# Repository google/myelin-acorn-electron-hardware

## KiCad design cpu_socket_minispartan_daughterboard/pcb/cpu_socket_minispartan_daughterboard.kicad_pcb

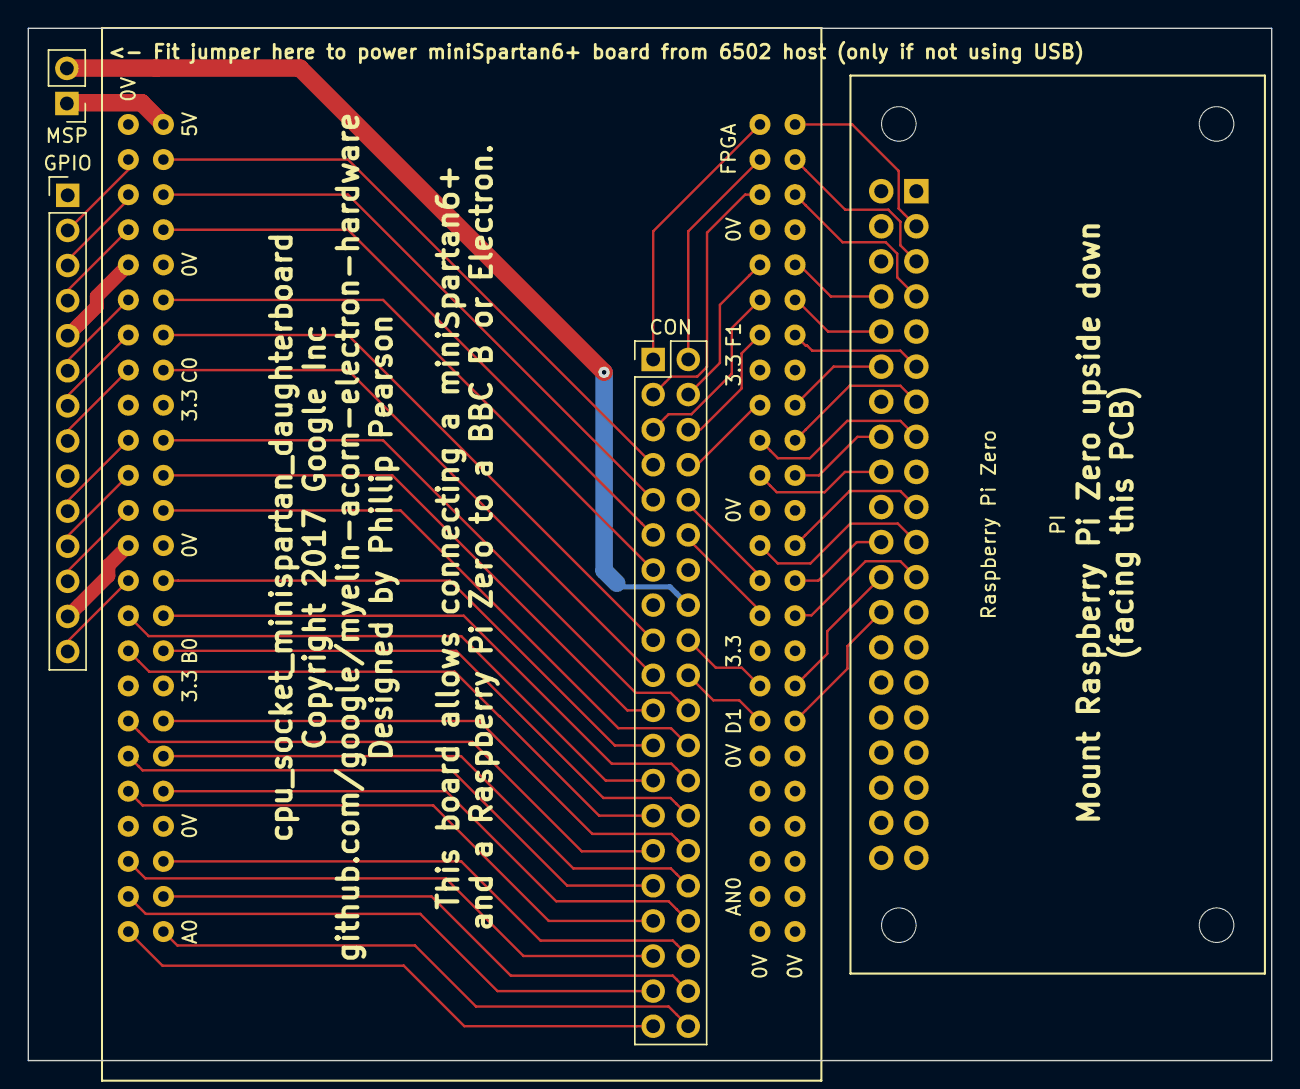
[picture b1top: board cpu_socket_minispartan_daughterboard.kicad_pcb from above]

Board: 2 copper layers, 90.0 x 74.7 mm, 5 parts (0 on the bottom side), 69 nets.

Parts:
CON: 2x20 connector for daughterboard; Pin_Header_Straight_2x20_Pitch2.54mm
FPGA: miniSpartan6+ board; scarab_mini_spartan_6_lx25
GPIO: some GPIO pins; Pin_Header_Straight_1x14_Pitch2.54mm
MSP: bbc to minispartan 5v; Pin_Header_Straight_1x02_Pitch2.54mm
PI: Raspberry Pi Zero; raspberry_pi_zero_flipped

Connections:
GND: CON.14, FPGA.GNDa, FPGA.GNDb, FPGA.GNDc, FPGA.GNDd, FPGA.GNDe, FPGA.GNDf, FPGA.GNDg, FPGA.GNDh, FPGA.GNDi, FPGA.GNDj, FPGA.GNDk, FPGA.GNDl, FPGA.GNDm, FPGA.GNDn, GPIO.1, GPIO.9, PI.9, PI.14, PI.20, PI.25
ext_5V: CON.16, MSP.2
ext_A0: CON.25, FPGA.B3
ext_A1: CON.26, FPGA.B2
ext_A2: CON.27, FPGA.B1
ext_A3: CON.28, FPGA.B0
ext_A4: CON.29, FPGA.A11
ext_A5: CON.30, FPGA.A10
ext_A6: CON.31, FPGA.A9
ext_A7: CON.32, FPGA.A8
ext_A8: CON.33, FPGA.A7
ext_A9: CON.34, FPGA.A6
ext_A10: CON.35, FPGA.A5
ext_A11: CON.36, FPGA.A4
ext_A12: CON.37, FPGA.A3
ext_A13: CON.38, FPGA.A2
ext_A14: CON.39, FPGA.A1
ext_A15: CON.40, FPGA.A0
ext_D0: CON.17, FPGA.C2
ext_D1: CON.18, FPGA.D3
ext_D2: CON.19, FPGA.C0
ext_D3: CON.20, FPGA.D1
ext_D4: CON.21, FPGA.B8
ext_D5: CON.22, FPGA.B10
ext_D6: CON.23, FPGA.B4
ext_D7: CON.24, FPGA.B6
ext_GP0: CON.1, FPGA.F11
ext_GP1: CON.2, FPGA.F9
ext_GP2: CON.3, FPGA.F7
ext_GP3: CON.4, FPGA.F5
ext_GP4: CON.5, FPGA.F3
ext_GP5: CON.6, FPGA.F1
ext_GP6: CON.7, FPGA.C10
ext_GP7: CON.8, FPGA.E11
ext_GP8: CON.9, FPGA.C8
ext_GP9: CON.10, FPGA.E3
ext_GP10: CON.11, FPGA.C6
ext_GP11: CON.12, FPGA.E1
ext_GP12: CON.13, FPGA.C4
minispartan_3V3c: FPGA.3V3c, GPIO.13
minispartan_3V3e: FPGA.3V3e, GPIO.5
minispartan_5v: FPGA.5V0, MSP.1
minispartan_B5: FPGA.B5, GPIO.14
minispartan_B7: FPGA.B7, GPIO.12
minispartan_B9: FPGA.B9, GPIO.11
minispartan_B11: FPGA.B11, GPIO.10
minispartan_C1: FPGA.C1, GPIO.8
minispartan_C3: FPGA.C3, GPIO.7
minispartan_C5: FPGA.C5, GPIO.6
minispartan_C7: FPGA.C7, GPIO.4
minispartan_C9: FPGA.C9, GPIO.3
minispartan_C11: FPGA.C11, GPIO.2
pi_serial_RX: FPGA.F2, PI.10
pi_serial_TX: FPGA.F4, PI.8
tube_A0: FPGA.E8, PI.13
tube_A1: FPGA.F10, PI.3
tube_A2: FPGA.F8, PI.5
tube_D0: FPGA.D2, PI.24
tube_D1: FPGA.E5, PI.21
tube_D2: FPGA.E4, PI.19
tube_D3: FPGA.E0, PI.23
tube_D4: FPGA.E9, PI.15
tube_D5: FPGA.E6, PI.16
tube_D6: FPGA.E7, PI.18
tube_D7: FPGA.E2, PI.22
tube_PHI0: FPGA.D0, PI.26
tube_RnW: FPGA.E10, PI.12
tube_nRST: FPGA.F6, PI.7
tube_nTUBE: FPGA.F0, PI.11

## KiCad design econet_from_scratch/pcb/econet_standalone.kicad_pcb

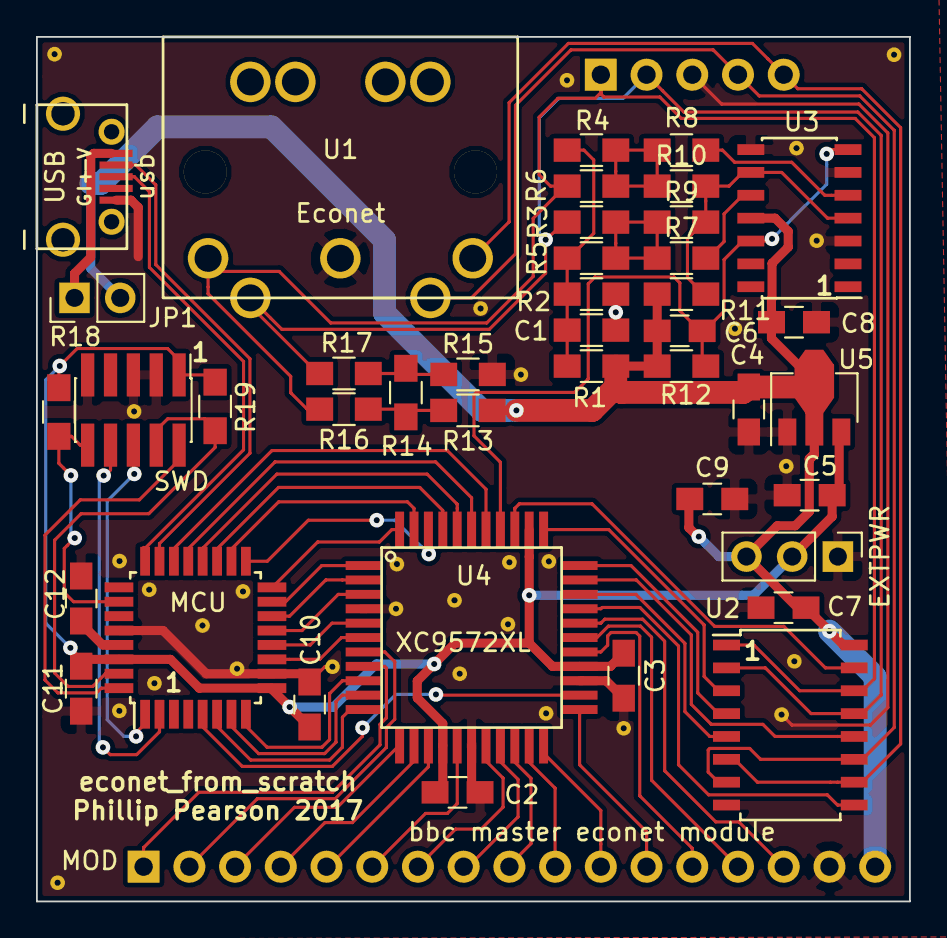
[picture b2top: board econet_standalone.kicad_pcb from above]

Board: 2 copper layers, 48.5 x 48.0 mm, 72 parts (0 on the bottom side), 62 nets.

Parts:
C1: 10u; R_0805_HandSoldering
C2, C3, C7, C8, C10, C11: 100n; C_0805_HandSoldering
C4, C5, C12: 1u; C_0805_HandSoldering
C6: 10n; C_0805_HandSoldering
C9: 10u; C_0805_HandSoldering
EXTPWR: ext pwr; Pin_Header_Straight_1x03_Pitch2.54mm
JP1: USB power; Pin_Header_Straight_1x02_Pitch2.54mm
MCU: ATSAMD21E18A; TQFP-32_7x7mm_Pitch0.8mm
MOD: bbc master econet module; bbc_master_econet_module
R1: 1k5; R_0805_HandSoldering
R2, R12, R13, R15, R19: 1k; R_0805_HandSoldering
R3, R4: 100k; R_0805_HandSoldering
R5, R6, R18: 10k; R_0805_HandSoldering
R7, R8, R9, R10: 56k; R_0805_HandSoldering
R11: 1M5; R_0805_HandSoldering
R14: 220R; R_0805_HandSoldering
R16, R17: 56R; R_0805_HandSoldering
SWD: swd; Pin_Header_Straight_2x05_Pitch1.27mm_SMD
U1: Econet; din_5_econet_pcb_mount
U2: SN65C1168; SOIC-16W_5.3x10.2mm_Pitch1.27mm
U3: LM319; SOIC-14_3.9x8.7mm_Pitch1.27mm
U4: XC9572XL; xilinx_vqg44
U5: MCP1700T-3302E/MB; SOT-89-3
USB: usb; micro_usb_b_smd_molex
staple_single1, staple_single2, staple_single3, staple_single4, staple_single5, staple_single6, staple_single7, staple_single8, staple_single9, staple_single10, staple_single11, staple_single12, staple_single13, staple_single14, staple_single15, staple_single16, staple_single17, staple_single18, staple_single19, staple_single20, staple_single21, staple_single22, staple_single23, staple_single24, staple_single25, staple_single26, staple_single27, staple_single28, staple_single29, staple_single30: via_single

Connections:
3V3: C2.1, C3.1, C5.1, C10.2, C11.2, EXTPWR.2, MCU.9, MCU.30, R18.2, R19.2, SWD.1, U4.15, U4.26, U4.35, U5.3
5V: C4.1, C6.2, C7.1, C8.1, C9.1, EXTPWR.3, JP1.2, MOD.17, R1.1, R11.2, R12.2, R13.1, U2.16, U3.11, U5.2
A0: MOD.5, U4.14
A1: MOD.6, U4.16
D0: MOD.7, U4.18
D1: MOD.8, U4.19
D2: MOD.9, U4.20
D3: MOD.10, U4.21
D4: MOD.11, U4.22
D5: MOD.12, U4.23
D6: MOD.13, U4.27
D7: MOD.14, U4.28
GND: C1.2, C2.2, C3.2, C4.2, C5.2, C7.2, C8.2, C9.2, C10.1, C11.1, C12.1, EXTPWR.1, MCU.10, MCU.28, MOD.16, MOD.E3, R2.2, R15.2, SWD.3, SWD.5, SWD.9, U1.2, U2.8, U3.3, U3.6, U3.8, U4.4, U4.17, U4.25, U5.1, USB.5, staple_single1.1, staple_single2.1, staple_single3.1, staple_single4.1, staple_single5.1, staple_single6.1, staple_single7.1, staple_single8.1, staple_single9.1, staple_single10.1, staple_single11.1, staple_single12.1, staple_single13.1, staple_single14.1, staple_single15.1, staple_single16.1, staple_single17.1, staple_single18.1, staple_single19.1, staple_single20.1, staple_single21.1, staple_single22.1, staple_single23.1, staple_single24.1, staple_single25.1, staple_single26.1, staple_single27.1, staple_single28.1, staple_single29.1, staple_single30.1
PA18: MCU.19, U4.41
PA19: MCU.20, U4.40
PA22: MCU.21, U4.39
PA23: MCU.22, U4.38
PHI2: MOD.4, U4.13
RnW: MOD.2, U4.7
SWCLK: MCU.31, R19.1, SWD.4
SWDIO: MCU.32, SWD.2
USBDM: MCU.23, USB.2
USBDP: MCU.24, USB.3
VDDCORE: C12.2, MCU.29
VUSB: JP1.1, USB.1
bias_M: R14.2, R15.1, R17.1
bias_P: R13.2, R14.1, R16.1
cd_vdiv_2v: C1.1, R1.2, R2.1, R5.2, R6.2
clock_24m: MCU.16, U4.44
collision_detect: C6.1, R12.1, U3.7, U3.12, U4.37
cpld_TCK: MCU.6, U4.11
cpld_TDI: MCU.8, U4.9
cpld_TDO: MCU.5, U4.24
cpld_TMS: MCU.7, U4.10
drive_econet_clock: MCU.17, U4.42
econet_centre: R9.2, R10.2, R11.1, U3.4, U3.9
econet_clock_D: U2.9, U4.30
econet_clock_DE: U2.12, U4.32
econet_clock_R: U2.5, U4.31
econet_clock_from_mcu: MCU.18, U4.43
econet_clock_line_N: MOD.E5, U1.3, U2.6, U2.10
econet_clock_line_P: MOD.E4, U1.5, U2.7, U2.11
econet_data_D: U2.15, U4.36
econet_data_DE: U2.4, U4.33
econet_data_R: U2.3, U4.34
econet_data_line_N: MOD.E2, R3.1, R17.2, U1.4, U2.2, U2.13
econet_data_line_P: MOD.E1, R4.1, R16.2, U1.1, U2.1, U2.14
econet_dm_div: R3.2, R5.1, R7.1, R9.1
econet_dp_div: R4.2, R6.1, R8.1, R10.1
lm319_dm_m: R7.2, U3.10
lm319_dp_m: R8.2, U3.5
mcu_RESET: MCU.26, R18.1, SWD.10
mcu_debug_RXD: MCU.2, SWD.8
mcu_debug_TXD: MCU.1, SWD.6
mcu_is_transmitting: MCU.14, U4.2
nADLC: MOD.3, U4.12
nNETINT: MOD.1, U4.8
nRESET: MOD.15, U4.29
outputting_frame: MCU.13, U4.3
serial_buffer_empty: MCU.12, U4.5
serial_cpld_to_mcu: MCU.15, U4.1
serial_mcu_to_cpld: MCU.11, U4.6

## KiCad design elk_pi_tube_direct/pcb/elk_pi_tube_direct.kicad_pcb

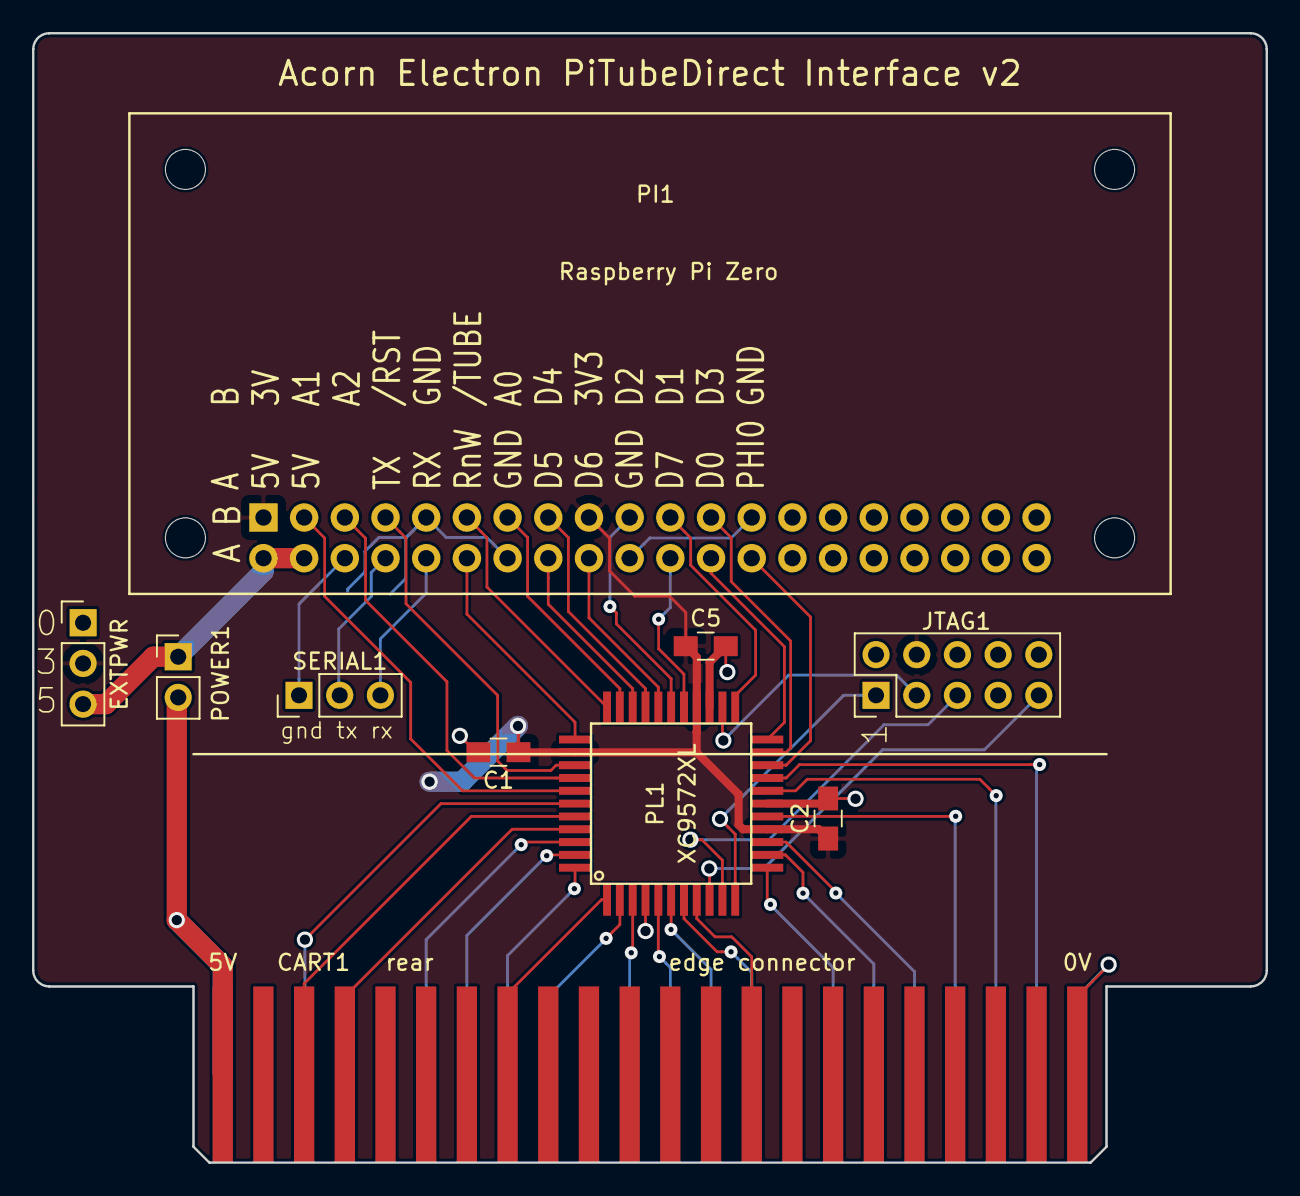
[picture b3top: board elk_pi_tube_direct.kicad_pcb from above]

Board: 2 copper layers, 77.0 x 70.5 mm, 10 parts (0 on the bottom side), 45 nets.

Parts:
C1, C2, C5: 100n; C_0805_HandSoldering
CART1: edge connector; acorn_electron_cartridge_edge_connector
EXTPWR: ext pwr; Pin_Header_Straight_1x03_Pitch2.54mm
JTAG1: jtag; Pin_Header_Straight_2x05_Pitch2.54mm
PI1: Raspberry Pi Zero; raspberry_pi_zero_flipped
PL1: XC9572XL; xilinx_vqg44
POWER1: Elk-Pi 5V; Pin_Header_Straight_1x02_Pitch2.54mm
SERIAL1: Pi Serial; Pin_Header_Straight_1x03_Pitch2.54mm

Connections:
3V3: C1.1, C2.1, C5.1, EXTPWR.2, JTAG1.4, PI1.1, PI1.17, PL1.15, PL1.26, PL1.35
5V: EXTPWR.3, PI1.2, PI1.4, POWER1.1
GND: C1.2, C2.2, C5.2, CART1.A22, CART1.B22, EXTPWR.1, JTAG1.2, JTAG1.10, PI1.9, PI1.14, PI1.20, PI1.25, PL1.4, PL1.17, PL1.25
cpld_TCK: JTAG1.1, PL1.11
cpld_TDI: JTAG1.9, PL1.9
cpld_TDO: JTAG1.3, PL1.24
cpld_TMS: JTAG1.5, PL1.10
elk_5V: CART1.A1, CART1.B1, POWER1.2
elk_A0: CART1.B18, PL1.14
elk_A1: CART1.B17, PL1.13
elk_A2: CART1.B16, PL1.12
elk_A4: CART1.B14, PL1.7
elk_A5: CART1.B13, PL1.6
elk_A6: CART1.B12, PL1.5
elk_A7: CART1.B11, PL1.3
elk_D0: CART1.B19, PL1.16
elk_D1: CART1.B21, PL1.19
elk_D2: CART1.B20, PL1.18
elk_D3: CART1.B3, PL1.39
elk_D4: CART1.B9, PL1.2
elk_D5: CART1.B8, PL1.44
elk_D6: CART1.B7, PL1.43
elk_D7: CART1.B6, PL1.42
elk_PHI0: CART1.A8, PL1.1
elk_RnW: CART1.A4, PL1.41
elk_nINFC: CART1.A14, PL1.8
elk_nRST: CART1.A3, PL1.40
pi_serial_GND: PI1.6, SERIAL1.1
pi_serial_RX: PI1.10, SERIAL1.3
pi_serial_TX: PI1.8, SERIAL1.2
tube_A0: PI1.13, PL1.32
tube_A1: PI1.3, PL1.38
tube_A2: PI1.5, PL1.37
tube_D0: PI1.24, PL1.22
tube_D1: PI1.21, PL1.23
tube_D2: PI1.19, PL1.28
tube_D3: PI1.23, PL1.21
tube_D4: PI1.15, PL1.30
tube_D5: PI1.16, PL1.31
tube_D6: PI1.18, PL1.29
tube_D7: PI1.22, PL1.27
tube_PHI0: PI1.26, PL1.20
tube_RnW: PI1.12, PL1.34
tube_nRST: PI1.7, PL1.36
tube_nTUBE: PI1.11, PL1.33

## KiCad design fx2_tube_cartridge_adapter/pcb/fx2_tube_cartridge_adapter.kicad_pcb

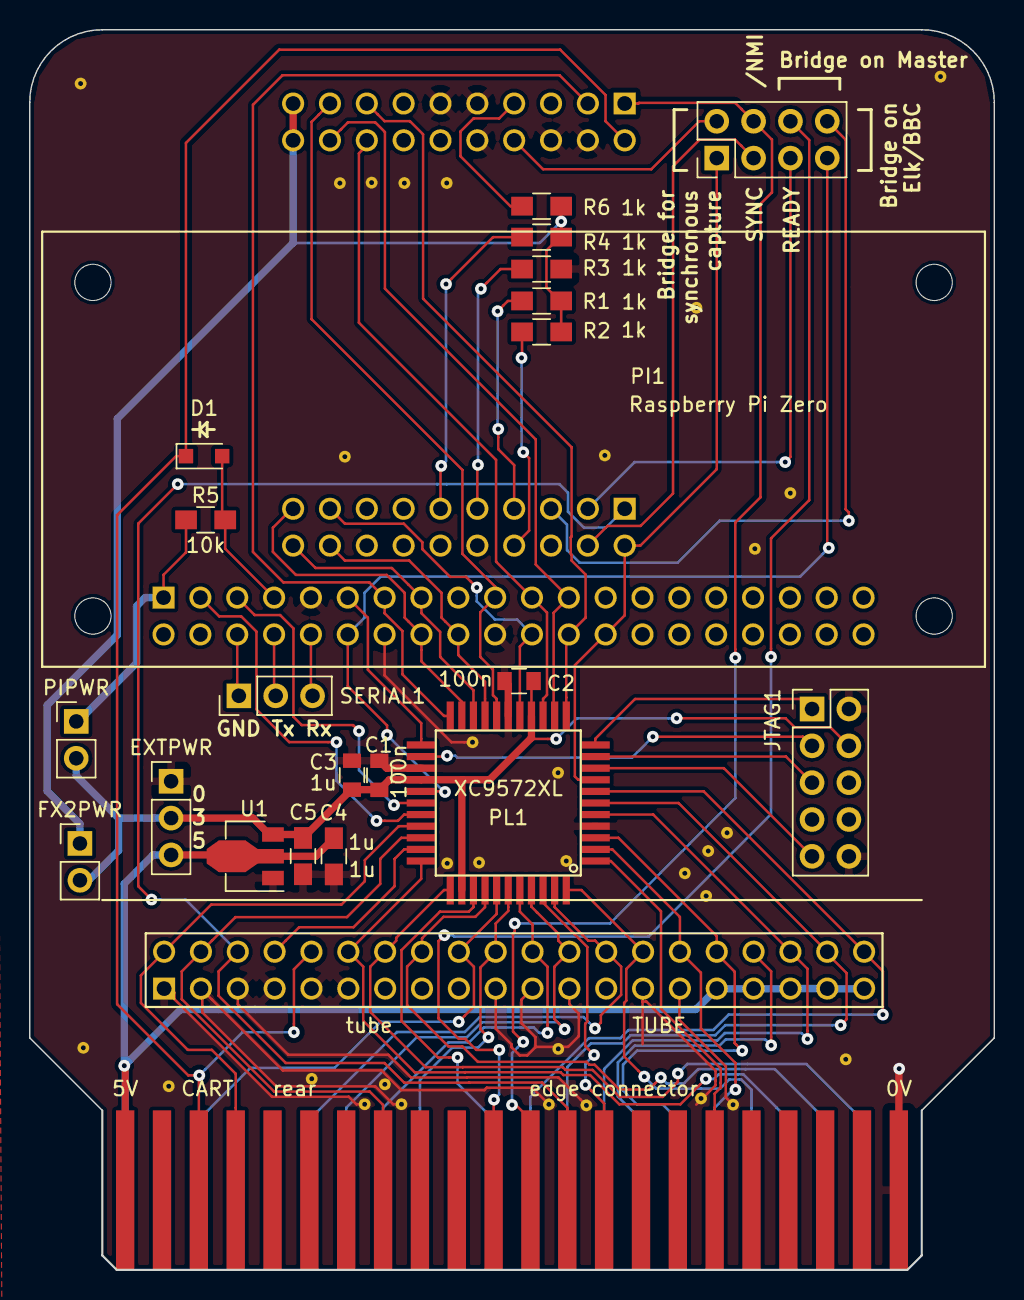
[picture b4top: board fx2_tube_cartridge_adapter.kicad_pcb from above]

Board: 2 copper layers, 66.5 x 85.5 mm, 56 parts (1 on the bottom side), 61 nets.

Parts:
C1, C2: 100n; C_0805
C3: 1u; C_0805
C4, C5: 1u; C_0805_HandSoldering
CART: edge connector; acorn_electron_cartridge_edge_connector
D1: BAT54; D_SOD-323_HandSoldering
EXTPWR: ext pwr; Pin_Header_Straight_1x03_Pitch2.54mm
FX2: lcsoft mini; lcsoft_mini_flipped
FX2PWR: Power from FX2; Pin_Header_Straight_1x02_Pitch2.54mm
JTAG1: jtag; Pin_Header_Straight_2x05_Pitch2.54mm
LEADS: Options; Pin_Header_Straight_2x04_Pitch2.54mm
PI1: Raspberry Pi Zero; raspberry_pi_zero_flipped
PIPWR: Power from Pi; Pin_Header_Straight_1x02_Pitch2.54mm
PL1: XC9572XL; xilinx_vqg44
R1, R2, R3, R4, R6: 1k; R_0805_HandSoldering
R5: 10k; R_0805_HandSoldering
SERIAL1: Pi Serial; Pin_Header_Straight_1x03_Pitch2.54mm
TUBE: tube; header_2x20_100mil
U1: MCP1700T-3302E/MB; SOT-89-3
staple_single1, staple_single2, staple_single3, staple_single4, staple_single5, staple_single6, staple_single7, staple_single8, staple_single9, staple_single10, staple_single11, staple_single12, staple_single13, staple_single14, staple_single15, staple_single16, staple_single17, staple_single18, staple_single19, staple_single20, staple_single21, staple_single22, staple_single23, staple_single24, staple_single25, staple_single26, staple_single27, staple_single28, staple_single29, staple_single30, staple_single31, staple_single32: via_single

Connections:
3V3: C1.1, C2.1, C3.1, C5.1, EXTPWR.2, FX2PWR.2, JTAG1.4, PIPWR.2, PL1.15, PL1.26, PL1.35, U1.3
3V3_FX2: FX2.L19, FX2.L20, FX2PWR.1, R1.2, R2.2, R4.2, R6.2
3V3_PI: PI1.1, PIPWR.1, R5.1
5V: C4.2, CART.A1, CART.B1, EXTPWR.3, TUBE.31, TUBE.33, TUBE.35, TUBE.37, TUBE.39, U1.2
GND: C1.2, C2.2, C3.2, C4.1, C5.2, CART.A22, CART.B22, EXTPWR.1, FX2.L4, FX2.L6, FX2.L9, FX2.L10, FX2.L11, JTAG1.2, JTAG1.10, PI1.9, PI1.14, PI1.20, PI1.25, PL1.4, PL1.17, PL1.25, R3.2, TUBE.1, TUBE.3, TUBE.5, TUBE.7, TUBE.9, TUBE.11, TUBE.13, TUBE.15, TUBE.17, TUBE.19, TUBE.21, TUBE.23, TUBE.25, TUBE.27, TUBE.29, U1.1, staple_single1.1, staple_single2.1, staple_single3.1, staple_single4.1, staple_single5.1, staple_single6.1, staple_single7.1, staple_single8.1, staple_single9.1, staple_single10.1, staple_single11.1, staple_single12.1, staple_single13.1, staple_single14.1, staple_single15.1, staple_single16.1, staple_single17.1, staple_single18.1, staple_single19.1, staple_single20.1, staple_single21.1, staple_single22.1, staple_single23.1, staple_single24.1, staple_single25.1, staple_single26.1, staple_single27.1, staple_single28.1, staple_single29.1, staple_single30.1, staple_single31.1, staple_single32.1
analyzer_PA2: FX2.R11, R4.1
analyzer_PA4: FX2.R9, R3.1
analyzer_PA5: FX2.R8, R2.1
analyzer_PA6: FX2.R7, R1.1
analyzer_PD0_RnW: FX2.R5, LEADS.8
analyzer_PD2_READY: FX2.R3, LEADS.5
analyzer_RDY0: FX2.L7, R6.1
bbc_nTUBE: PL1.32, TUBE.8
cpld_TCK: JTAG1.1, PL1.11
cpld_TDI: JTAG1.9, PL1.9
cpld_TDO: JTAG1.3, PL1.24
cpld_TMS: JTAG1.5, PL1.10
cpu_A0: CART.B18, PL1.44, TUBE.28
cpu_A1: CART.B17, PL1.2, TUBE.30
cpu_A2: CART.B16, PL1.3, TUBE.32
cpu_A3: CART.B15, TUBE.34
cpu_A4: CART.B14, PL1.5, TUBE.36
cpu_A5: CART.B13, PL1.6, TUBE.38
cpu_A6: CART.B12, PL1.7, TUBE.40
cpu_A7: CART.B11, PL1.36
cpu_CLK: CART.A8, PL1.31, TUBE.4
cpu_D0: CART.B19, PL1.33, TUBE.12
cpu_D1: CART.B21, PL1.34, TUBE.14
cpu_D2: CART.B20, PL1.37, TUBE.16
cpu_D3: CART.B3, PL1.38, TUBE.18
cpu_D4: CART.B9, PL1.39, TUBE.20
cpu_D5: CART.B8, PL1.40, TUBE.22
cpu_D6: CART.B7, PL1.41, TUBE.24
cpu_D7: CART.B6, PL1.43, TUBE.26
cpu_RnW: CART.A4, PL1.30, TUBE.2
cpu_SYNC: FX2.R4, LEADS.3
cpu_nIRQ: CART.A13, FX2.R1, TUBE.6
cpu_nNMI: CART.A12, FX2.L1, LEADS.4
cpu_nRST: CART.A3, D1.1, FX2.L2, TUBE.10
elk_16MHz: CART.A17, PL1.1
elk_READY_master_RnW: CART.A11, LEADS.6
elk_nINFC: CART.A14, PL1.42
pi_serial_GND: PI1.6, SERIAL1.1
pi_serial_RX: PI1.10, SERIAL1.3
pi_serial_TX: PI1.8, SERIAL1.2
tube_A0: FX2.L3, PI1.13, PL1.22
tube_A1: PI1.3, PL1.29
tube_A2: PI1.5, PL1.28
tube_CLK: FX2.R2, LEADS.1, PI1.26, PL1.8
tube_CLK_jumper: FX2.L8, LEADS.2
tube_D0: FX2.L15, PI1.24, PL1.12
tube_D1: FX2.L16, PI1.21, PL1.14
tube_D2: FX2.L17, PI1.19, PL1.18
tube_D3: FX2.L18, PI1.23, PL1.13
tube_D4: FX2.R20, PI1.15, PL1.20
tube_D5: FX2.R19, PI1.16, PL1.21
tube_D6: FX2.R18, PI1.18, PL1.19
tube_D7: FX2.R17, PI1.22, PL1.16
tube_RnW: LEADS.7, PI1.12, PL1.27
tube_nRST: D1.2, PI1.7, R5.2
tube_nTUBE: PI1.11, PL1.23

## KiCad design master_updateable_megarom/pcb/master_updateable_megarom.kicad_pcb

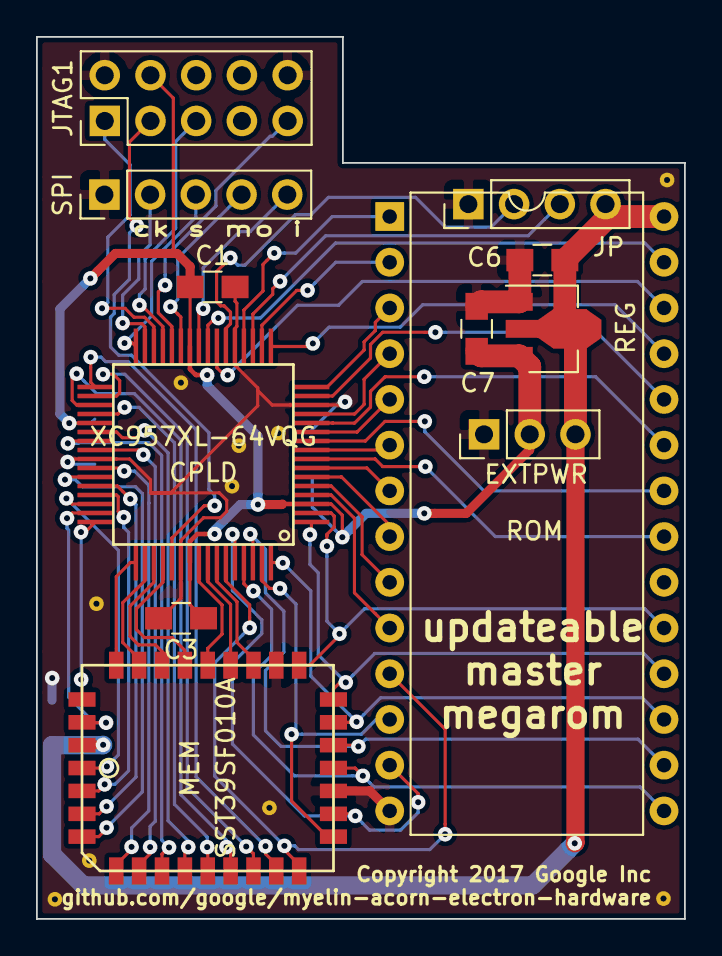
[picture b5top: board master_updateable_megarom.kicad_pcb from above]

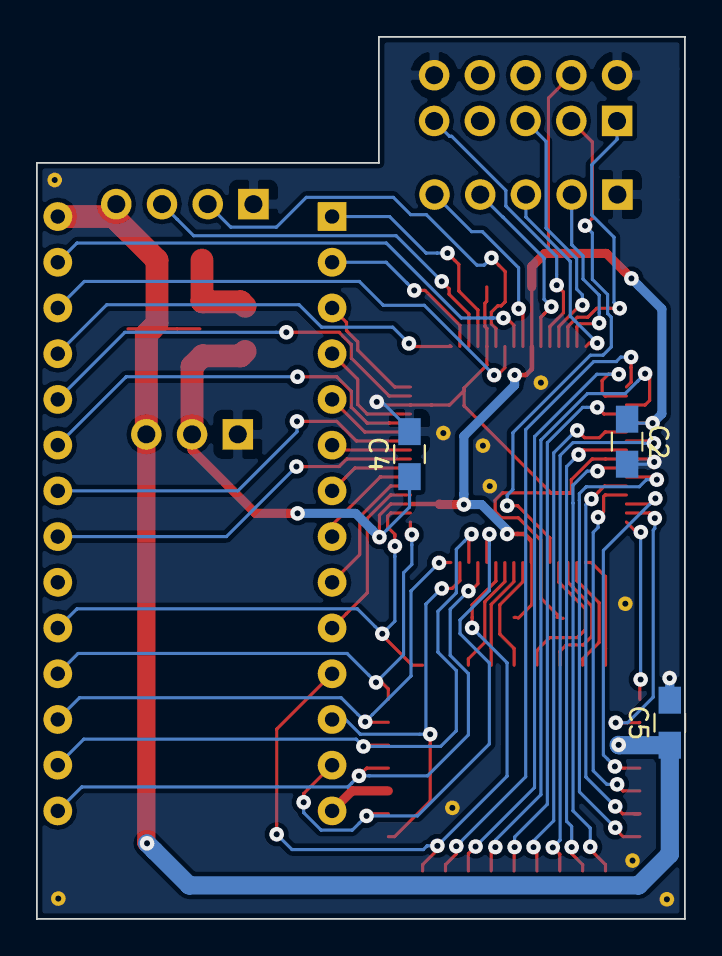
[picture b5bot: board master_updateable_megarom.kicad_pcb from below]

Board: 2 copper layers, 36.0 x 49.0 mm, 25 parts (3 on the bottom side), 59 nets.

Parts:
C1, C2, C3, C4, C5: 100n; C_0805_HandSoldering
C6, C7: 1u; C_0805_HandSoldering
CPLD: XC957XL-64VQG; xilinx_vqg64
EXTPWR: ext pwr; Pin_Header_Straight_1x03_Pitch2.54mm
JP: jumpers; Pin_Header_Straight_1x04_Pitch2.54mm
JTAG1: jtag; Pin_Header_Straight_2x05_Pitch2.54mm
MEM: SST39SF010A; sst_plcc32_nh
REG: MCP1700T-3302E/MB; SOT-89-3
ROM: MOS ROM; DIP-28_W15.24mm
SPI: spi; Pin_Header_Straight_1x05_Pitch2.54mm
staple_single1, staple_single2, staple_single3, staple_single4, staple_single5, staple_single6, staple_single7, staple_single8, staple_single9, staple_single10: via_single

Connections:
3V3: C1.1, C2.1, C3.1, C4.1, C7.1, CPLD.3, CPLD.26, CPLD.37, CPLD.55, EXTPWR.2, JTAG1.4, REG.3
5V: C5.1, C6.2, EXTPWR.3, JP.4, MEM.32, REG.2, ROM.28
D0: CPLD.59, MEM.13, ROM.11
D1: CPLD.63, MEM.14, ROM.12
D2: CPLD.60, MEM.15, ROM.13
D3: CPLD.61, MEM.17, ROM.15
D4: CPLD.62, MEM.18, ROM.16
D5: CPLD.64, MEM.19, ROM.17
D6: CPLD.1, MEM.20, ROM.18
D7: CPLD.2, MEM.21, ROM.19
GND: C1.2, C2.2, C3.2, C4.2, C5.2, C6.1, C7.2, CPLD.14, CPLD.21, CPLD.41, CPLD.54, EXTPWR.1, JP.1, JTAG1.2, JTAG1.10, MEM.16, MEM.22, REG.1, ROM.14, SPI.1, staple_single1.1, staple_single2.1, staple_single3.1, staple_single4.1, staple_single5.1, staple_single6.1, staple_single7.1, staple_single8.1, staple_single9.1, staple_single10.1
bbc_A0: CPLD.4, ROM.10
bbc_A1: CPLD.5, ROM.9
bbc_A2: CPLD.6, ROM.8
bbc_A3: CPLD.7, ROM.7
bbc_A4: CPLD.9, ROM.6
bbc_A5: CPLD.11, ROM.5
bbc_A6: CPLD.13, ROM.4
bbc_A7: CPLD.16, ROM.3
bbc_A8: CPLD.17, ROM.25
bbc_A9: CPLD.15, ROM.24
bbc_A10: CPLD.8, ROM.21
bbc_A11: CPLD.12, ROM.23
bbc_A12: CPLD.18, ROM.2
bbc_A13: CPLD.23, ROM.26
bbc_A14: CPLD.24, ROM.27
bbc_A15: CPLD.20, ROM.1
bbc_A16: CPLD.10, ROM.22
cpld_JP0: CPLD.22, JP.2
cpld_JP1: CPLD.19, JP.3
cpld_MISO: CPLD.25, SPI.5
cpld_MOSI: CPLD.27, SPI.4
cpld_SCK: CPLD.31, SPI.2
cpld_SS: CPLD.32, SPI.3
cpld_TCK: CPLD.30, JTAG1.1
cpld_TDI: CPLD.28, JTAG1.9
cpld_TDO: CPLD.53, JTAG1.3
cpld_TMS: CPLD.29, JTAG1.5
flash_A0: CPLD.33, MEM.12
flash_A1: CPLD.34, MEM.11
flash_A2: CPLD.35, MEM.10
flash_A3: CPLD.36, MEM.9
flash_A4: CPLD.38, MEM.8
flash_A5: CPLD.39, MEM.7
flash_A6: CPLD.40, MEM.6
flash_A7: CPLD.42, MEM.5
flash_A8: CPLD.51, MEM.27
flash_A9: CPLD.52, MEM.26
flash_A10: CPLD.58, MEM.23
flash_A11: CPLD.56, MEM.25
flash_A12: CPLD.43, MEM.4
flash_A13: CPLD.50, MEM.28
flash_A14: CPLD.49, MEM.29
flash_A15: CPLD.44, MEM.3
flash_A16: CPLD.45, MEM.2
flash_A17: CPLD.48, MEM.30
flash_A18: CPLD.46, MEM.1
flash_nOE: CPLD.57, MEM.24
flash_nWE: CPLD.47, MEM.31

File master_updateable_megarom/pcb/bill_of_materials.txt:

Identifier	Value	Description	KiCad package
C1	100n	100n capacitor in 0805 package	Capacitors_SMD:C_0805_HandSoldering
C2	100n	100n capacitor in 0805 package	Capacitors_SMD:C_0805_HandSoldering
C3	100n	100n capacitor in 0805 package	Capacitors_SMD:C_0805_HandSoldering
C4	100n	100n capacitor in 0805 package	Capacitors_SMD:C_0805_HandSoldering
C5	100n	100n capacitor in 0805 package	Capacitors_SMD:C_0805_HandSoldering
C6	1u	1u capacitor in 0805 package	Capacitors_SMD:C_0805_HandSoldering
C7	1u	1u capacitor in 0805 package	Capacitors_SMD:C_0805_HandSoldering
CPLD	XC9572XL-64VQG	Xilinx XC9572XL in 64-pin 0.5mm TQFP package.  Any speed or temperature grade is OK.	myelin-kicad:xilinx_vqg64
EXTPWR	ext pwr	1x3 0.1 inch male header	Pin_Headers:Pin_Header_Straight_1x03_Pitch2.54mm
JP	jumpers	1x4 0.1 inch male header	Pin_Headers:Pin_Header_Straight_1x04_Pitch2.54mm
JTAG1	jtag	2x5 header for JTAG programming.  Use generic 0.1 inch header strip or Digikey ED1543-ND.	Pin_Headers:Pin_Header_Straight_2x05_Pitch2.54mm
MEM	SST39SF010A/020A/040	128kB/256kB/512kB flash chip in SST 'NH' PLCC-32 package: SST39SF040-XX-XX-NHE, SST39SF020A-XX-XX-NHE, or SST39SF010A-XX-XX-NHE	myelin-kicad:sst_plcc32_nh
REG	MCP1700T-3302E/MB	3.3V LDO regulator, e.g. Digikey MCP1700T3302EMBCT-ND.  Search for the exact part number because there are many variants.	TO_SOT_Packages_SMD:SOT-89-3
ROM	MOS ROM	Adapter to emulate a 600mil 28-pin DIP, e.g. Digikey 1175-1525-5-ND	Housings_DIP:DIP-28_W15.24mm
SPI	spi	1x3 0.1 inch male header	Pin_Headers:Pin_Header_Straight_1x05_Pitch2.54mm

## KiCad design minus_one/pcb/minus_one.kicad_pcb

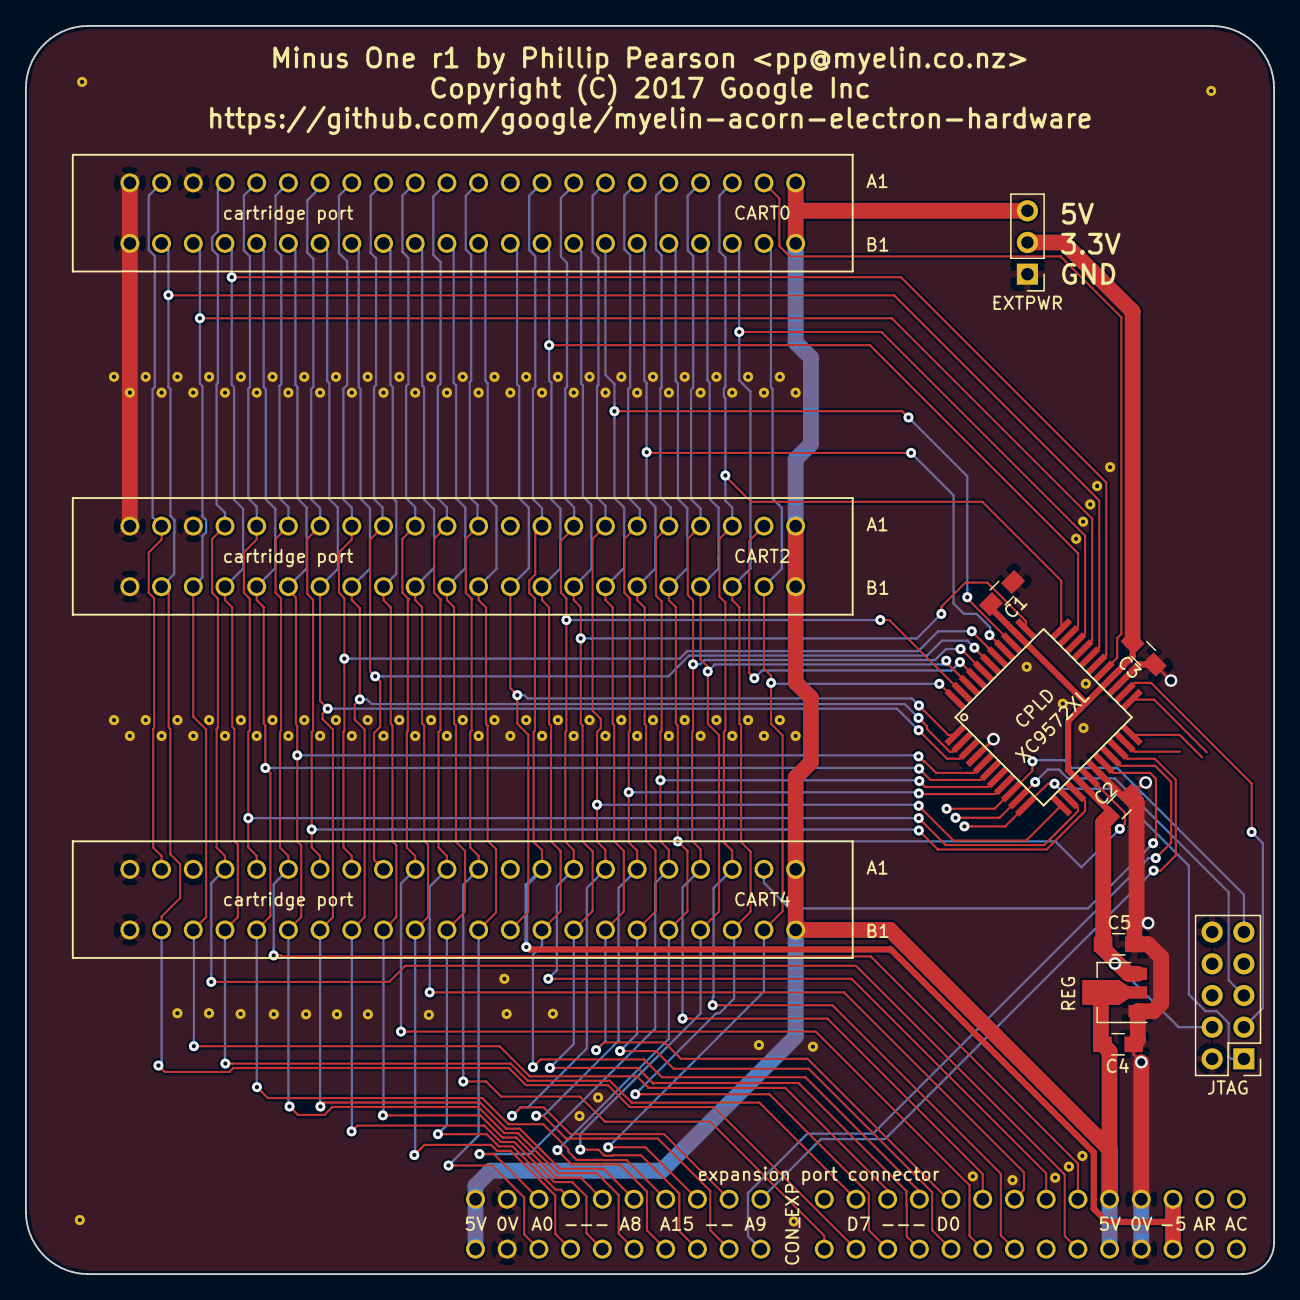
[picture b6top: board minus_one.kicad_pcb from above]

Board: 2 copper layers, 100.0 x 100.0 mm, 48 parts (0 on the bottom side), 49 nets.

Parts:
C1, C2, C3: 100n; C_0805_HandSoldering
C4, C5: 1u; C_0805_HandSoldering
CART0, CART2, CART4: cartridge port; acorn_electron_cartridge_socket
CON_EXP: expansion port connector; acorn_electron_48pin_expansion_connector
CPLD: XC9572XL; xilinx_vqg44
EXTPWR: ext pwr; Pin_Header_Straight_1x03_Pitch2.54mm
JTAG: jtag; Pin_Header_Straight_2x05_Pitch2.54mm
REG: MCP1700T-3302E/MB; SOT89-3_Housing
staple1, staple2: via_zigzag_1x44_2.54mm
staple_single1, staple_single2, staple_single3, staple_single4, staple_single5, staple_single6, staple_single7, staple_single8, staple_single9, staple_single10, staple_single11, staple_single12, staple_single13, staple_single14, staple_single15, staple_single16, staple_single17, staple_single18, staple_single19, staple_single20, staple_single21, staple_single22, staple_single23, staple_single24, staple_single25, staple_single26, staple_single27, staple_single28, staple_single29, staple_single30, staple_single31, staple_single32, staple_single33: via_single

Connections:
3V3: C1.1, C2.1, C3.1, C5.1, CPLD.15, CPLD.26, CPLD.35, EXTPWR.2, JTAG.4, REG.3
5V: C4.1, CART0.A1, CART0.B1, CART2.A1, CART2.B1, CART4.A1, CART4.B1, CON_EXP.9, CON_EXP.10, CON_EXP.49, CON_EXP.50, EXTPWR.3, REG.2
16MHZ: CART0.A17, CART2.A17, CART4.A17, CON_EXP.12
-5V: CART0.A9, CART2.A9, CART4.A9, CON_EXP.5, CON_EXP.6
A0: CART0.B18, CART2.B18, CART4.B18, CON_EXP.38, CPLD.6
A1: CART0.B17, CART2.B17, CART4.B17, CON_EXP.39, CPLD.5
A2: CART0.B16, CART2.B16, CART4.B16, CON_EXP.40, CPLD.3
A3: CART0.B15, CART2.B15, CART4.B15, CON_EXP.41, CPLD.2
A4: CART0.B14, CART2.B14, CART4.B14, CON_EXP.42
A5: CART0.B13, CART2.B13, CART4.B13, CON_EXP.43
A6: CART0.B12, CART2.B12, CART4.B12, CON_EXP.44
A7: CART0.B11, CART2.B11, CART4.B11, CON_EXP.45
A8: CART0.A5, CART2.A5, CART4.A5, CON_EXP.46, CPLD.7
A9: CART0.B5, CART2.B5, CART4.B5, CON_EXP.37, CPLD.16
A10: CART0.B2, CART2.B2, CART4.B2, CON_EXP.36, CPLD.44
A11: CART0.B4, CART2.B4, CART4.B4, CON_EXP.35, CPLD.42
A12: CART0.A7, CART2.A7, CART4.A7, CON_EXP.34, CPLD.12
A13: CART0.A6, CART2.A6, CART4.A6, CON_EXP.33, CPLD.8
A14: CON_EXP.32, CPLD.20
A15: CON_EXP.31, CPLD.19
ADIN: CART0.A21, CART2.A21, CART4.A21
D0: CART0.B19, CART2.B19, CART4.B19, CON_EXP.26, CPLD.28
D1: CART0.B21, CART2.B21, CART4.B21, CON_EXP.25, CPLD.29
D2: CART0.B20, CART2.B20, CART4.B20, CON_EXP.24, CPLD.30
D3: CART0.B3, CART2.B3, CART4.B3, CON_EXP.23, CPLD.31
D4: CART0.B9, CART2.B9, CART4.B9, CON_EXP.22, CPLD.32
D5: CART0.B8, CART2.B8, CART4.B8, CON_EXP.21, CPLD.34
D6: CART0.B7, CART2.B7, CART4.B7, CON_EXP.20, CPLD.36
D7: CART0.B6, CART2.B6, CART4.B6, CON_EXP.19, CPLD.37
GND: C1.2, C2.2, C3.2, C4.2, C5.2, CART0.A20, CART0.A22, CART0.B22, CART2.A20, CART2.A22, CART2.B22, CART4.A20, CART4.A22, CART4.B22, CON_EXP.7, CON_EXP.8, CON_EXP.47, CON_EXP.48, CPLD.4, CPLD.17, CPLD.25, EXTPWR.1, JTAG.2, JTAG.10, REG.1, staple1.1, staple1.2, staple1.3, staple1.4, staple1.5, staple1.6, staple1.7, staple1.8, staple1.9, staple1.10, staple1.11, staple1.12, staple1.13, staple1.14, staple1.15, staple1.16, staple1.17, staple1.18, staple1.19, staple1.20, staple1.21, staple1.22, staple1.23, staple1.24, staple1.25, staple1.26, staple1.27, staple1.28, staple1.29, staple1.30, staple1.31, staple1.32, staple1.33, staple1.34, staple1.35, staple1.36, staple1.37, staple1.38, staple1.39, staple1.40, staple1.41, staple1.42, staple1.43, staple1.44, staple2.1, staple2.2, staple2.3, staple2.4, staple2.5, staple2.6, staple2.7, staple2.8, staple2.9, staple2.10, staple2.11, staple2.12, staple2.13, staple2.14, staple2.15, staple2.16, staple2.17, staple2.18, staple2.19, staple2.20, staple2.21, staple2.22, staple2.23, staple2.24, staple2.25, staple2.26, staple2.27, staple2.28, staple2.29, staple2.30, staple2.31, staple2.32, staple2.33, staple2.34, staple2.35, staple2.36, staple2.37, staple2.38, staple2.39, staple2.40, staple2.41, staple2.42, staple2.43, staple2.44, staple_single1.1, staple_single2.1, staple_single3.1, staple_single4.1, staple_single5.1, staple_single6.1, staple_single7.1, staple_single8.1, staple_single9.1, staple_single10.1, staple_single11.1, staple_single12.1, staple_single13.1, staple_single14.1, staple_single15.1, staple_single16.1, staple_single17.1, staple_single18.1, staple_single19.1, staple_single20.1, staple_single21.1, staple_single22.1, staple_single23.1, staple_single24.1, staple_single25.1, staple_single26.1, staple_single27.1, staple_single28.1, staple_single29.1, staple_single30.1, staple_single31.1, staple_single32.1, staple_single33.1
PHI0: CART0.A8, CART2.A8, CART4.A8, CON_EXP.14, CPLD.43
RnW: CART0.A4, CART2.A4, CART4.A4, CON_EXP.18, CPLD.40
SOUND_OUT: CART0.A19, CART2.A19, CART4.A19, CON_EXP.11
cart0_nOE: CART0.A2, CPLD.27
cart2_nOE: CART2.A2, CPLD.41
cart4_nOE: CART4.A2, CPLD.18
cart_ROMQA: CART0.A16, CART2.A16, CART4.A16, CPLD.14
cart_nINFC: CART0.A14, CART2.A14, CART4.A14, CPLD.39
cart_nINFD: CART0.A15, CART2.A15, CART4.A15, CPLD.38
cart_nOE2: CART0.B10, CART2.B10, CART4.B10, CPLD.1
cart_nROMSTB: CART0.A18, CART2.A18, CART4.A18, CPLD.13
cpld_TCK: CPLD.11, JTAG.1
cpld_TDI: CPLD.9, JTAG.9
cpld_TDO: CPLD.24, JTAG.3
cpld_TMS: CPLD.10, JTAG.5
nIRQ: CART0.A13, CART2.A13, CART4.A13, CON_EXP.17
nNMI: CART0.A12, CART2.A12, CART4.A12, CON_EXP.16
nRDY: CART0.A11, CART2.A11, CART4.A11, CON_EXP.27
nRST: CART0.A3, CART2.A3, CART4.A3, CON_EXP.15, CPLD.33

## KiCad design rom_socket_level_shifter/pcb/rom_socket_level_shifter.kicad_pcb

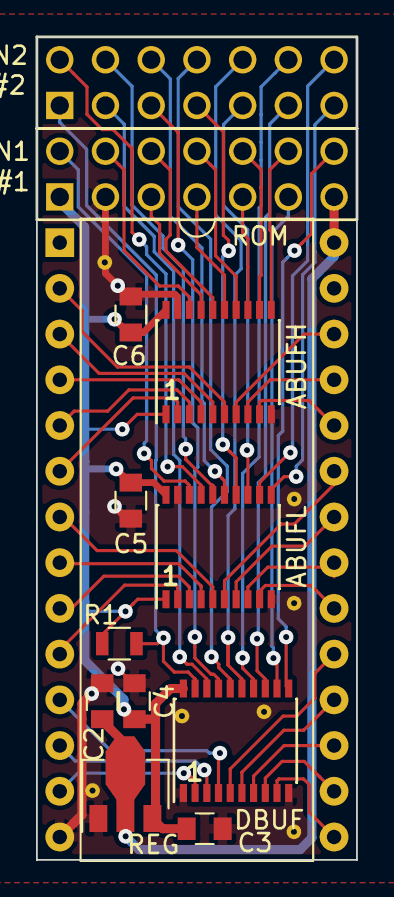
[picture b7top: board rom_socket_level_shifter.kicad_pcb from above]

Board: 2 copper layers, 17.8 x 45.7 mm, 20 parts (0 on the bottom side), 52 nets.

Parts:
ABUFH: 74LVC245; SSOP-20_4.4x6.5mm_Pitch0.65mm
ABUFL: 74LVC245; SSOP-20_4.4x6.5mm_Pitch0.65mm
C2, C3: 1u; C_0805
C4, C5, C6: 100n; C_0805
CON1: 3.3V #1; header_2x07_100mil
CON2: 3.3V #2; header_2x07_100mil
DBUF: 74LVC245; SSOP-20_4.4x6.5mm_Pitch0.65mm
R1: 19k; R_0805
REG: MCP1700T-3302E/MB; SOT-89-3
ROM: BBC ROM; DIP-28_W15.24mm
staple_single1, staple_single2, staple_single3, staple_single4, staple_single5, staple_single6, staple_single7: via_single

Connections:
3V3: ABUFH.1, ABUFH.20, ABUFL.1, ABUFL.20, C3.1, C4.2, C5.2, C6.2, CON1.1, DBUF.20, R1.2, REG.3
5V: C2.2, CON1.13, REG.2, ROM.28
A0: ABUFL.2, ROM.10
A1: ABUFL.3, ROM.9
A2: ABUFL.4, ROM.8
A3: ABUFL.5, ROM.7
A4: ABUFH.2, ROM.6
A5: ABUFH.3, ROM.5
A6: ABUFH.4, ROM.4
A7: ABUFH.5, ROM.3
A8: ABUFH.8, ROM.25
A9: ABUFH.9, ROM.24
A10: ABUFL.8, ROM.21
A11: ABUFL.6, ROM.23
A12: ABUFH.6, ROM.2
A13: ABUFH.7, ROM.26
D0: DBUF.4, ROM.11
D1: DBUF.3, ROM.12
D2: DBUF.2, ROM.13
D3: DBUF.9, ROM.15
D4: DBUF.8, ROM.16
D5: DBUF.7, ROM.17
D6: DBUF.6, ROM.18
D7: DBUF.5, ROM.19
GND: ABUFH.10, ABUFH.19, ABUFL.10, ABUFL.19, C2.1, C3.2, C4.1, C5.1, C6.1, CON1.3, DBUF.1, DBUF.10, REG.1, ROM.14, staple_single1.1, staple_single2.1, staple_single3.1, staple_single4.1, staple_single5.1, staple_single6.1, staple_single7.1
ext_A0: ABUFL.11, CON2.13
ext_A1: ABUFL.12, CON2.14
ext_A2: ABUFL.13, CON2.9
ext_A3: ABUFL.14, CON2.7
ext_A4: ABUFH.11, CON1.12
ext_A5: ABUFH.12, CON1.10
ext_A6: ABUFH.13, CON1.9
ext_A7: ABUFH.14, CON1.8
ext_A8: ABUFH.17, CON1.5
ext_A9: ABUFH.18, CON1.4
ext_A10: ABUFL.17, CON2.2
ext_A11: ABUFL.15, CON2.6
ext_A12: ABUFH.15, CON1.7
ext_A13: ABUFH.16, CON1.6
ext_D0: CON2.11, DBUF.13
ext_D1: CON1.11, DBUF.12
ext_D2: CON1.14, DBUF.11
ext_D3: CON2.3, DBUF.18
ext_D4: CON2.5, DBUF.17
ext_D5: CON2.8, DBUF.16
ext_D6: CON2.10, DBUF.15
ext_D7: CON2.12, DBUF.14
ext_dbuf_nCE: CON2.1, DBUF.19, R1.1
ext_nCS: ABUFL.18, CON1.2
ext_nOE: ABUFL.16, CON2.4
nCS: ABUFL.9, ROM.20
nOE: ABUFL.7, ROM.22

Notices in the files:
elk_pi_tube_direct/pcb/elk_pi_tube_direct.py:
Copyright 2017 Google Inc.
Licensed under the Apache License, Version 2.0 (the "License");
econet_from_scratch/pcb/econet_standalone.kicad_pcb:
Copyright 2017 Google LLC
minus_one/pcb/minus_one.kicad_pcb:
Copyright (C) 2017 Google Inc
